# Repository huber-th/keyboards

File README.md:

# Custom Keyboards

This repository contains files for my custom keyboards.

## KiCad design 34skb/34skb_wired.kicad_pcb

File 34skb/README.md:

# 34skb - 34 key split keyboard

34skb (34 split keyboard) is a 34 key split keyboard heavily inspired by the [sweep](https://github.com/davidphilipbarr/Sweep) and [ferris](https://github.com/pierrechevalier83/ferris).

The keyboard can be built either as a wired or wireless version.

## Features

- Choc switches (PG1350)
- Choc spacing (18x17mm)
- Kailh hot-swap socket
- Pro-Micro ATmega32U4 MCU (wired) or Nice!Nano v2 (ble)

## Required Hardware

| Amount | Item Description                                                  |
|:------:|:------------------------------------------------------------------|
| 2      | ATmega32U4 MCU (or other Pro-Micro compatible)                    |
| 2      | PCB (wired or ble depending on the chosen chip)                   |
| 2      | 3.7v 110mAh 301230 rechargeable lithium battery (for ble version) |
| 34     | Choc switch (PG1350)                                              |
| 34     | Kailh hot-swap socket                                             |
| 2      | TRRS jack (for wired version)                                     |
| 1      | TRSS cable (for wired version)                                    |

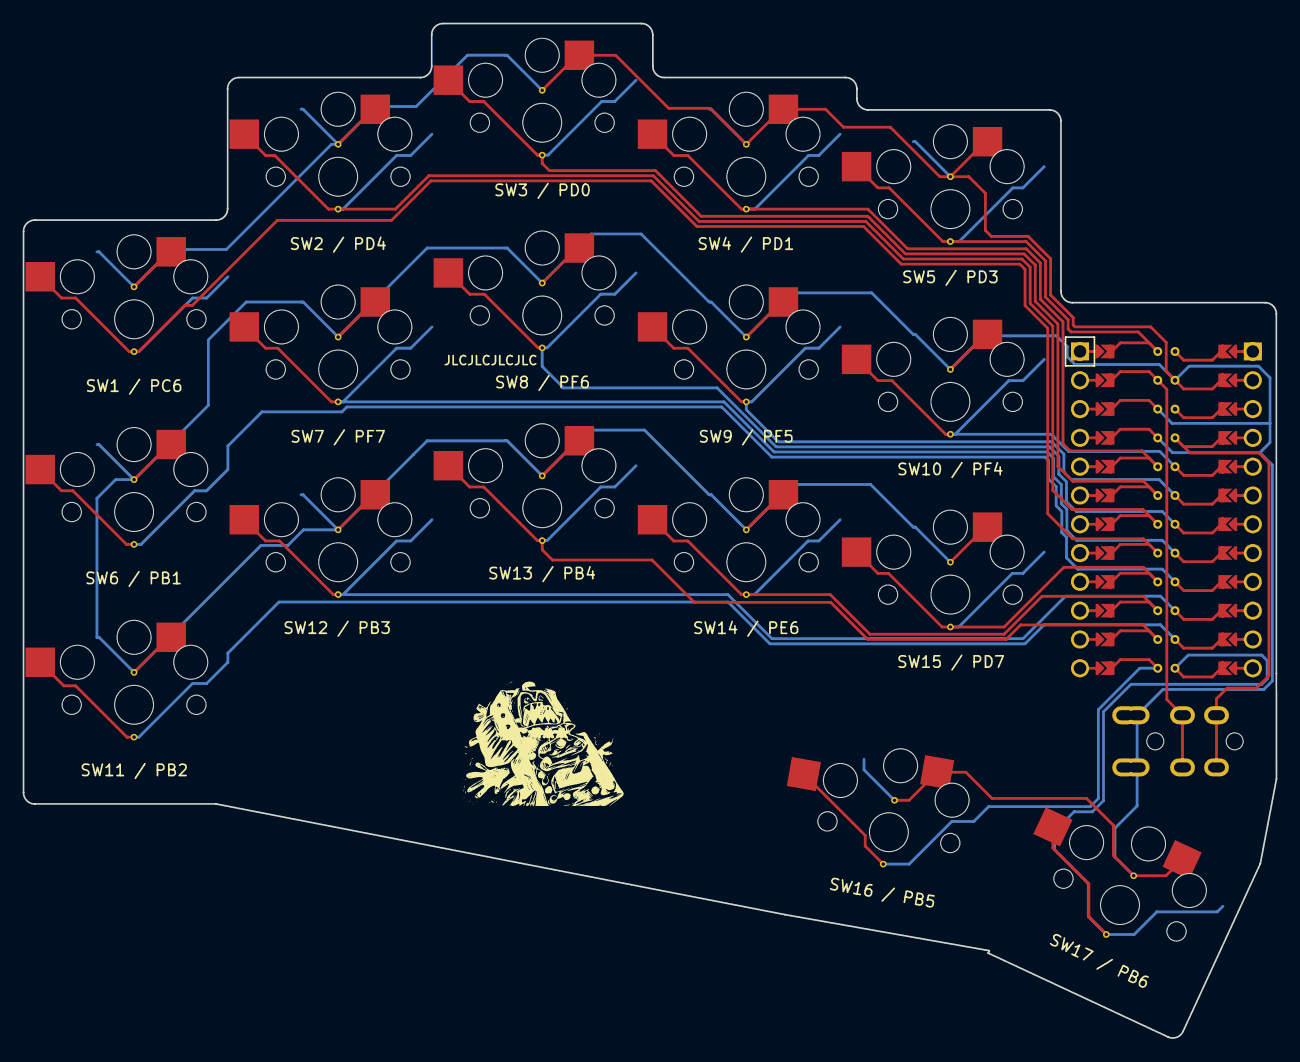
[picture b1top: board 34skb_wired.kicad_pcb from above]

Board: 2 copper layers, 110.5 x 89.5 mm, 18 parts (0 on the bottom side), 18 nets.

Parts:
MCU1: ProMicro
S1, S2, S3, S4, S5, S6, S7, S8, S9, S10, S11, S12, S13, S14, S15, S16, S17: PG1350

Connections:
GND: MCU1.2, MCU1.21, MCU1.22, S1.1, S2.1, S3.1, S4.1, S5.1, S6.1, S7.1, S8.1, S9.1, S10.1, S11.1, S12.1, S13.1, S14.1, S15.1, S16.1, S17.1
matrix_index_bottom: MCU1.15, S10.2
matrix_index_home: MCU1.6, S11.2
matrix_index_top: MCU1.20, S12.2
matrix_inner_bottom: MCU1.16, S13.2
matrix_inner_home: MCU1.5, S14.2
matrix_inner_top: MCU1.24, S15.2
matrix_middle_bottom: MCU1.14, S7.2
matrix_middle_home: MCU1.7, S8.2
matrix_middle_top: MCU1.19, S9.2
matrix_pinky_bottom: MCU1.11, S1.2
matrix_pinky_home: MCU1.9, S2.2
matrix_pinky_top: MCU1.17, S3.2
matrix_ring_bottom: MCU1.10, S4.2
matrix_ring_home: MCU1.8, S5.2
matrix_ring_top: MCU1.18, S6.2
thumb_left: MCU1.13, S16.2
thumb_right: MCU1.12, S17.2

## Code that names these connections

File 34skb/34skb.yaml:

points:
  zones:
    matrix:
      columns:
        pinky:
          rows:
            bottom:
              bind: [0,0,0,1]
            home:
              bind: [0,0,0,1]
            top:
              bind: [0,0,0,1]
        ring:
          spread: cx
          stagger: 0.66U
          rows:
            bottom:
              bind: [0,1,14,1]
            home:
              bind: [0,1,0,1]
            top:
              bind: [0,1,0,1]
        middle:
          spread: cx
          stagger: 0.25U
          rows:
            bottom:
              bind: [0,0,20,0]
            home:
              bind: [0,0,0,0]
            top:
              bind: [0,1,0,1]
        index:
          spread: cx
          stagger: -0.25U
          rows:
            bottom:
              bind: [0,1,20,1]
            home:
              bind: [0,1,0,1]
            top:
              bind: [0,1,0,1]
        inner:
          spread: cx
          stagger: -0.15U
          rows:
            bottom:
              bind: [0,20,0,0]
            home:
              bind: [0,20,0,0]
            top:
              bind: [0,1,0,0]
      rows:
        bottom:
        home:
        top:
    thumb:
      anchor:
        ref: matrix_index_bottom
        shift: [0.66U, -1.25U]
        rotate: -10
      columns:
        left:
          key.name: thumb_left
          rows:
            single:
              bind: [8,9,0,0]
        right:
          spread: U
          rotate: -15
          origin: [-0.5U, -0.5U]
          key.name: thumb_right
          rows:
            single:
              bind: [15,1,0,0]
  key:
    padding: cy
    footprints:
      - type: choc
        nets:
          from: GND
          to: =name
        params:
          hotswap: true
          reverse: true
          keycaps: true
outlines:
  exports:
    raw:
      - type: keys
        side: left
        size: [1cx - 0.5, 1cx - 0.5]
    cutout:
      - type: outline
        name: raw
        fillet: 1
    keycap_outline:
      - type: keys
        side: left
        size: [1cx -0.5, 1cy - 0.5]
        bound: false
pcbs:
  34skb:
    outlines:
      board:
        outline: cutout
      keycaps:
        outline: keycap_outline
        layer: Eco1.User
    footprints:
      mcu:
        type: promicro_pretty
        anchor:
          - ref: matrix_inner_home
            shift: [1U, -0.5U]
            rotate: -90
        nets:
          P1: matrix_inner_top
          P2: matrix_index_top
          P3: matrix_middle_top
          P4: matrix_ring_top
          P5: matrix_pinky_top
          P6: matrix_inner_bottom
          P7: matrix_index_bottom
          P8: matrix_middle_bottom
          P9: thumb_left
          P10: thumb_right
          P14: matrix_ring_bottom
          P15: matrix_pinky_home
          P16: matrix_pinky_bottom
          P18: matrix_ring_home
          P19: matrix_middle_home
          P20: matrix_index_home
          P21: matrix_inner_home
      trrs:
        type: trrs
        anchor:
          - ref: matrix_inner_bottom
            shift: [1.4U, -0.8U]
            rotate: -90
        nets:
          A: GND
          B: GND
          C: P0
          D: VCC
        params:
          reverse: true
          symmetric: true
      via_pinky_bottom:
        type: via
        nets:
          net: matrix_pinky_bottom
        anchor:
          - ref: matrix_pinky_bottom
            shift: [0U, -0.15U]
      via_pinky_home:
        type: via
        nets:
          net: matrix_pinky_home
        anchor:
          - ref: matrix_pinky_home
            shift: [0U, -0.15U]
      via_pinky_top:
        type: via
        nets:
          net: matrix_pinky_top
        anchor:
          - ref: matrix_pinky_top
            shift: [0U, -0.15U]
      via_ring_bottom:
        type: via
        nets:
          net: matrix_ring_bottom
        anchor:
          - ref: matrix_ring_bottom
            shift: [0U, -0.15U]
      via_ring_home:
        type: via
        nets:
          net: matrix_ring_home
        anchor:
          - ref: matrix_ring_home
            shift: [0U, -0.15U]
      via_ring_top:
        type: via
        nets:
          net: matrix_ring_top
        anchor:
          - ref: matrix_ring_top
            shift: [0U, -0.15U]
      via_middle_bottom:
        type: via
        nets:
          net: matrix_middle_bottom
        anchor:
          - ref: matrix_middle_bottom
            shift: [0U, -0.15U]
      via_middle_home:
        type: via
        nets:
          net: matrix_middle_home
        anchor:
          - ref: matrix_middle_home
            shift: [0U, -0.15U]
      via_middle_top:
        type: via
        nets:
          net: matrix_middle_top
        anchor:
          - ref: matrix_middle_top
            shift: [0U, -0.15U]
      via_index_bottom:
        type: via
        nets:
          net: matrix_index_bottom
        anchor:
          - ref: matrix_index_bottom
            shift: [0U, -0.15U]
      via_index_home:
        type: via
        nets:
          net: matrix_index_home
        anchor:
          - ref: matrix_index_home
            shift: [0U, -0.15U]
      via_index_top:
        type: via
        nets:
          net: matrix_index_top
        anchor:
          - ref: matrix_index_top
            shift: [0U, -0.15U]
      via_inner_bottom:
        type: via
        nets:
          net: matrix_inner_bottom
        anchor:
          - ref: matrix_inner_bottom
            shift: [0U, -0.15U]
      via_inner_home:
        type: via
        nets:
          net: matrix_inner_home
        anchor:
          - ref: matrix_inner_home
            shift: [0U, -0.15U]
      via_inner_top:
        type: via
        nets:
          net: matrix_inner_top
        anchor:
          - ref: matrix_inner_top
            shift: [0U, -0.15U]
      via_thumb_right:
        type: via
        nets:
          net: thumb_right
        anchor:
          - ref: thumb_right
            shift: [0U, -0.15U]
      via_thumb_left:
        type: via
        nets:
          net: thumb_left
        anchor:
          - ref: thumb_left
            shift: [0U, -0.15U]
      via_gnd_pinky_bottom:
        type: via
        nets:
          net: GND
        anchor:
          - ref: matrix_pinky_bottom
            shift: [0U, 0.15U]
      via_gnd_pinky_home:
        type: via
        nets:
          net: GND
        anchor:
          - ref: matrix_pinky_home
            shift: [0U, 0.15U]
      via_gnd_pinky_top:
        type: via
        nets:
          net: GND
        anchor:
          - ref: matrix_pinky_top
            shift: [0U, 0.15U]
      via_gnd_ring_bottom:
        type: via
        nets:
          net: GND
        anchor:
          - ref: matrix_ring_bottom
            shift: [0U, 0.15U]
      via_gnd_ring_home:
        type: via
        nets:
          net: GND
        anchor:
          - ref: matrix_ring_home
            shift: [0U, 0.15U]
      via_gnd_ring_top:
        type: via
        nets:
          net: GND
        anchor:
          - ref: matrix_ring_top
            shift: [0U, 0.15U]
      via_gnd_middle_bottom:
        type: via
        nets:
          net: GND
        anchor:
          - ref: matrix_middle_bottom
            shift: [0U, 0.15U]
      via_gnd_middle_home:
        type: via
        nets:
          net: GND
        anchor:
          - ref: matrix_middle_home
            shift: [0U, 0.15U]
      via_gnd_middle_top:
        type: via
        nets:
          net: GND
        anchor:
          - ref: matrix_middle_top
            shift: [0U, 0.15U]
      via_gnd_index_bottom:
        type: via
        nets:
          net: GND
        anchor:
          - ref: matrix_index_bottom
            shift: [0U, 0.15U]
      via_gnd_index_home:
        type: via
        nets:
          net: GND
        anchor:
          - ref: matrix_index_home
            shift: [0U, 0.15U]
      via_gnd_index_top:
        type: via
        nets:
          net: GND
        anchor:
          - ref: matrix_index_top
            shift: [0U, 0.15U]
      via_gnd_inner_bottom:
        type: via
        nets:
          net: GND
        anchor:
          - ref: matrix_inner_bottom
            shift: [0U, 0.15U]
      via_gnd_inner_home:
        type: via
        nets:
          net: GND
        anchor:
          - ref: matrix_inner_home
            shift: [0U, 0.15U]
      via_gnd_inner_top:
        type: via
        nets:
          net: GND
        anchor:
          - ref: matrix_inner_top
            shift: [0U, 0.15U]
      via_gnd_thumb_right:
        type: via
        nets:
          net: GND
        anchor:
          - ref: thumb_right
            shift: [0U, 0.15U]
      via_gnd_thumb_left:
        type: via
        nets:
          net: GND
        anchor:
          - ref: thumb_left
            shift: [0U, 0.15U]

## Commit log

2022-11-27 [34skb] Add keyboard files
